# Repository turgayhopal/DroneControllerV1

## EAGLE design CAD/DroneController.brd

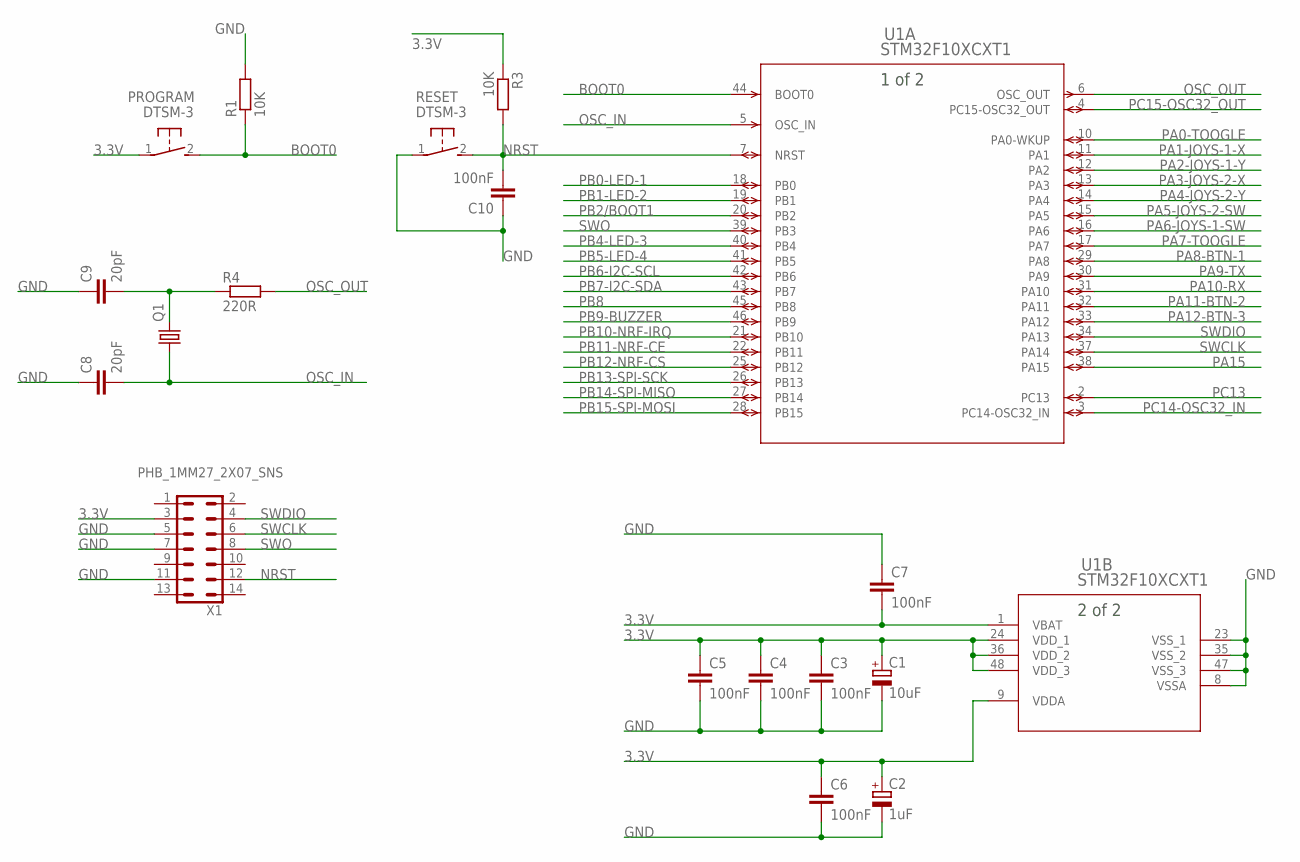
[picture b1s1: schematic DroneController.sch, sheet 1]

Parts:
C1: 10uF; SMC_A
C2: 1uF; SMC_A
C3, C4, C5, C6, C7, C10: 100nF; C0805
C8, C9: 20pF; C0805
PROGRAM: DTSM-3
Q1: CRYSTALHC49S; HC49/S
R1, R3: 10K; R0805
R4: 220R; R0805
RESET: DTSM-3
U1: STM32F10XCXT1; LQFP48-7X7MM
X1: PHB_1MM27_2X07_SNS

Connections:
3.3V: C1.+, C2.+, C3.1, C4.1, C5.1, C6.1, C7.2, PROGRAM.1, R3.1, U1.1 (VBAT), U1.9 (VDDA), U1.24 (VDD_1), U1.36 (VDD_2), U1.48 (VDD_3), X1.3; also elsewhere on the board
BOOT0: PROGRAM.2, R1.1, U1.44 (BOOT0)
GND: C1.-, C2.-, C3.2, C4.2, C5.2, C6.2, C7.1, C8.1, C9.1, C10.1, R1.2, RESET.1, U1.8 (VSSA), U1.23 (VSS_1), U1.35 (VSS_2), U1.47 (VSS_3), X1.5, X1.7, X1.11; also elsewhere on the board
unnamed: C9.2, Q1.2, R4.1
NRST: C10.2, R3.2, RESET.2, U1.7 (NRST), X1.12
OSC_IN: C8.2, Q1.1, U1.5 (OSC_IN)
OSC_OUT: R4.2, U1.6 (OSC_OUT)
PA0-TOOGLE: U1.10 (PA0-WKUP); also elsewhere on the board
PA1-JOYS-1-X: U1.11 (PA1); also elsewhere on the board
PA2-JOYS-1-Y: U1.12 (PA2); also elsewhere on the board
PA3-JOYS-2-X: U1.13 (PA3); also elsewhere on the board
PA4-JOYS-2-Y: U1.14 (PA4); also elsewhere on the board
PA5-JOYS-2-SW: U1.15 (PA5); also elsewhere on the board
PA6-JOYS-1-SW: U1.16 (PA6); also elsewhere on the board
PA7-TOOGLE: U1.17 (PA7)
PA8-BTN-1: U1.29 (PA8); also elsewhere on the board
PA9-TX: U1.30 (PA9)
PA10-RX: U1.31 (PA10)
PA11-BTN-2: U1.32 (PA11); also elsewhere on the board
PA12-BTN-3: U1.33 (PA12); also elsewhere on the board
PA15: U1.38 (PA15)
PB0-LED-1: U1.18 (PB0); also elsewhere on the board
PB1-LED-2: U1.19 (PB1); also elsewhere on the board
PB2/BOOT1: U1.20 (PB2)
PB4-LED-3: U1.40 (PB4); also elsewhere on the board
PB5-LED-4: U1.41 (PB5); also elsewhere on the board
PB6-I2C-SCL: U1.42 (PB6); also elsewhere on the board
PB7-I2C-SDA: U1.43 (PB7); also elsewhere on the board
PB8: U1.45 (PB8)
PB9-BUZZER: U1.46 (PB9)
PB10-NRF-IRQ: U1.21 (PB10); also elsewhere on the board
PB11-NRF-CE: U1.22 (PB11); also elsewhere on the board
PB12-NRF-CS: U1.25 (PB12); also elsewhere on the board
PB13-SPI-SCK: U1.26 (PB13); also elsewhere on the board
PB14-SPI-MISO: U1.27 (PB14); also elsewhere on the board
PB15-SPI-MOSI: U1.28 (PB15); also elsewhere on the board
PC13: U1.2 (PC13)
PC14-OSC32_IN: U1.3 (PC14-OSC32_IN)
PC15-OSC32_OUT: U1.4 (PC15-OSC32_OUT)
SWCLK: U1.37 (PA14), X1.6
SWDIO: U1.34 (PA13), X1.4
SWO: U1.39 (PB3), X1.8

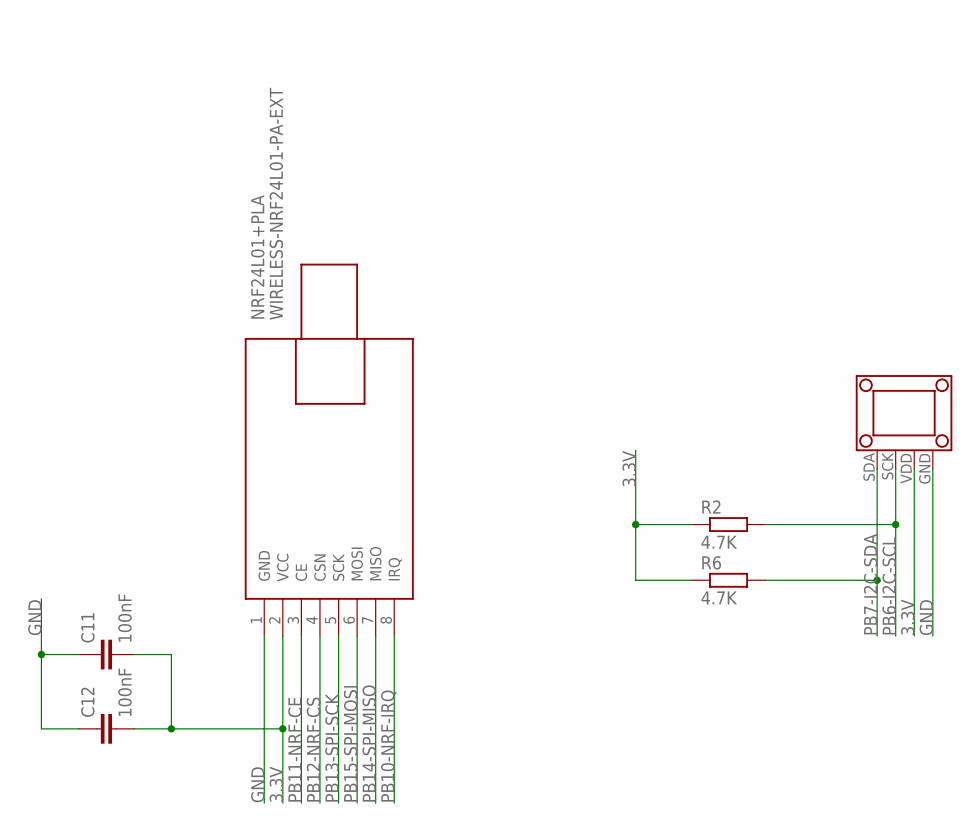
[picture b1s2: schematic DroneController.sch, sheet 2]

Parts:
C11, C12: 100nF; C0805
NRF24L01+PLA: WIRELESS-NRF24L01-PA-EXT
R2, R6: 4.7K; R0805
U$1: 1.3_TFT_OLED

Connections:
3.3V: C11.2, C12.2, NRF24L01+PLA.2 (VCC), R2.1, R6.1, U$1.VDD; also elsewhere on the board
GND: C11.1, C12.1, NRF24L01+PLA.1 (GND), U$1.GND; also elsewhere on the board
PB6-I2C-SCL: R2.2, U$1.SCK; also elsewhere on the board
PB7-I2C-SDA: R6.2, U$1.SDA; also elsewhere on the board
PB10-NRF-IRQ: NRF24L01+PLA.8 (IRQ); also elsewhere on the board
PB11-NRF-CE: NRF24L01+PLA.3 (CE); also elsewhere on the board
PB12-NRF-CS: NRF24L01+PLA.4 (CSN); also elsewhere on the board
PB13-SPI-SCK: NRF24L01+PLA.5 (SCK); also elsewhere on the board
PB14-SPI-MISO: NRF24L01+PLA.7 (MISO); also elsewhere on the board
PB15-SPI-MOSI: NRF24L01+PLA.6 (MOSI); also elsewhere on the board

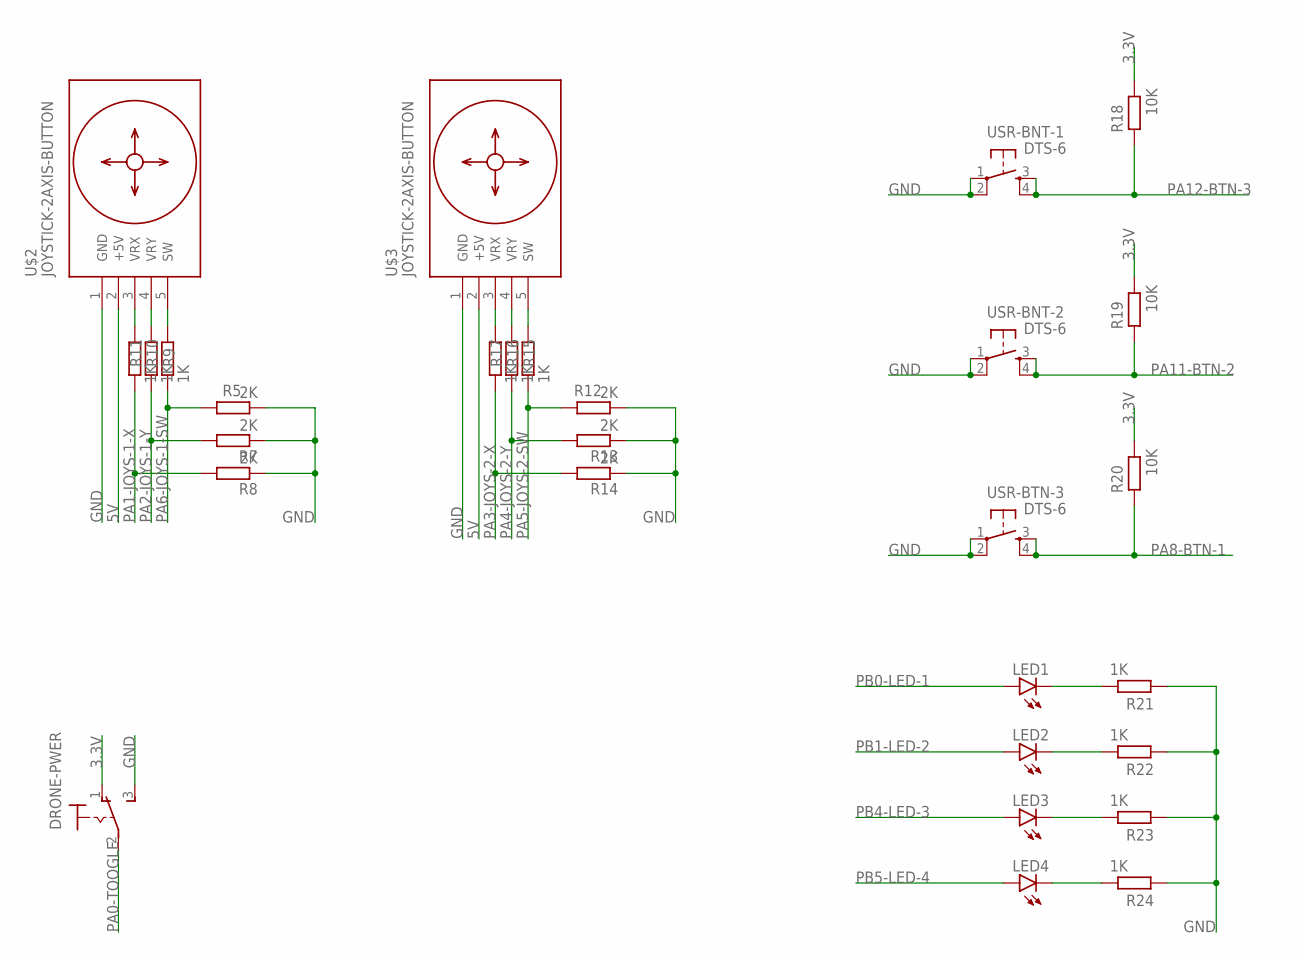
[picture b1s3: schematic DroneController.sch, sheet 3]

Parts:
DRONE-PWER: M9040P
LED1, LED2, LED3, LED4: LEDCHIP-LED0805; CHIP-LED0805
R5, R7, R8, R12, R13, R14: 2K; R0805
R9, R10, R11, R15, R16, R17, R21, R22, R23, R24: 1K; R0805
R18, R19, R20: 10K; R0805
U$2, U$3: JOYSTICK-2AXIS-BUTTON
USR-BNT-1, USR-BNT-2: DTS-6
USR-BTN-3: DTS-6

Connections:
3.3V: DRONE-PWER.1 (O), R18.1, R19.1, R20.1; also elsewhere on the board
5V: U$2.2 (+5V), U$3.2 (+5V); also elsewhere on the board
GND: DRONE-PWER.3 (S), R5.1, R7.1, R8.1, R12.1, R13.1, R14.1, R21.2, R22.2, R23.2, R24.2, U$2.1 (GND), U$3.1 (GND), USR-BNT-1.1, USR-BNT-1.2, USR-BNT-2.1, USR-BNT-2.2, USR-BTN-3.1, USR-BTN-3.2; also elsewhere on the board
unnamed: R11.2, U$2.3 (VRX)
unnamed: R10.2, U$2.4 (VRY)
unnamed: R9.2, U$2.5 (SW)
unnamed: R17.2, U$3.3 (VRX)
unnamed: R16.2, U$3.4 (VRY)
unnamed: LED4.C, R24.1
unnamed: R15.2, U$3.5 (SW)
unnamed: LED3.C, R23.1
unnamed: LED2.C, R22.1
unnamed: LED1.C, R21.1
PA0-TOOGLE: DRONE-PWER.2; also elsewhere on the board
PA1-JOYS-1-X: R8.2, R11.1; also elsewhere on the board
PA2-JOYS-1-Y: R7.2, R10.1; also elsewhere on the board
PA3-JOYS-2-X: R14.2, R17.1; also elsewhere on the board
PA4-JOYS-2-Y: R13.2, R16.1; also elsewhere on the board
PA5-JOYS-2-SW: R12.2, R15.1; also elsewhere on the board
PA6-JOYS-1-SW: R5.2, R9.1; also elsewhere on the board
PA8-BTN-1: R20.2, USR-BTN-3.3, USR-BTN-3.4; also elsewhere on the board
PA11-BTN-2: R19.2, USR-BNT-2.3, USR-BNT-2.4; also elsewhere on the board
PA12-BTN-3: R18.2, USR-BNT-1.3, USR-BNT-1.4; also elsewhere on the board
PB0-LED-1: LED1.A; also elsewhere on the board
PB1-LED-2: LED2.A; also elsewhere on the board
PB4-LED-3: LED3.A; also elsewhere on the board
PB5-LED-4: LED4.A; also elsewhere on the board

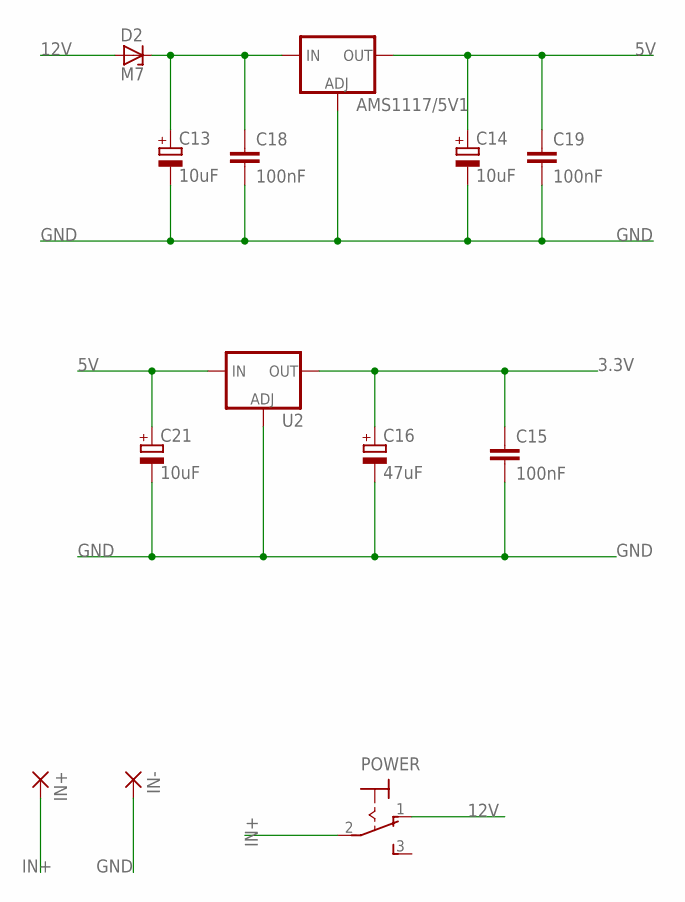
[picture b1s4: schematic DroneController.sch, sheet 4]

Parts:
AMS1117/5V1: V_REG_LM1117SOT223; SOT223
C13, C14, C21: 10uF; SMC_A
C15, C18, C19: 100nF; C0805
C16: 47uF; SMC_B
D2: M7; DO214AC
IN+: 2,15/1,0
IN-: 2,15/1,0
POWER: M9040P
U2: V_REG_LM1117SOT223; SOT223

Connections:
3.3V: C15.1, C16.+, U2.2 (OUT), U2.4 (OUT); also elsewhere on the board
5V: AMS1117/5V1.2 (OUT), AMS1117/5V1.4 (OUT), C14.+, C19.1, C21.+, U2.3 (IN); also elsewhere on the board
12V: D2.A, POWER.1 (O)
GND: AMS1117/5V1.1 (ADJ), C13.-, C14.-, C15.2, C16.-, C18.2, C19.2, C21.-, IN-.1, U2.1 (ADJ); also elsewhere on the board
IN+: IN+.1, POWER.2
unnamed: AMS1117/5V1.3 (IN), C13.+, C18.1, D2.C

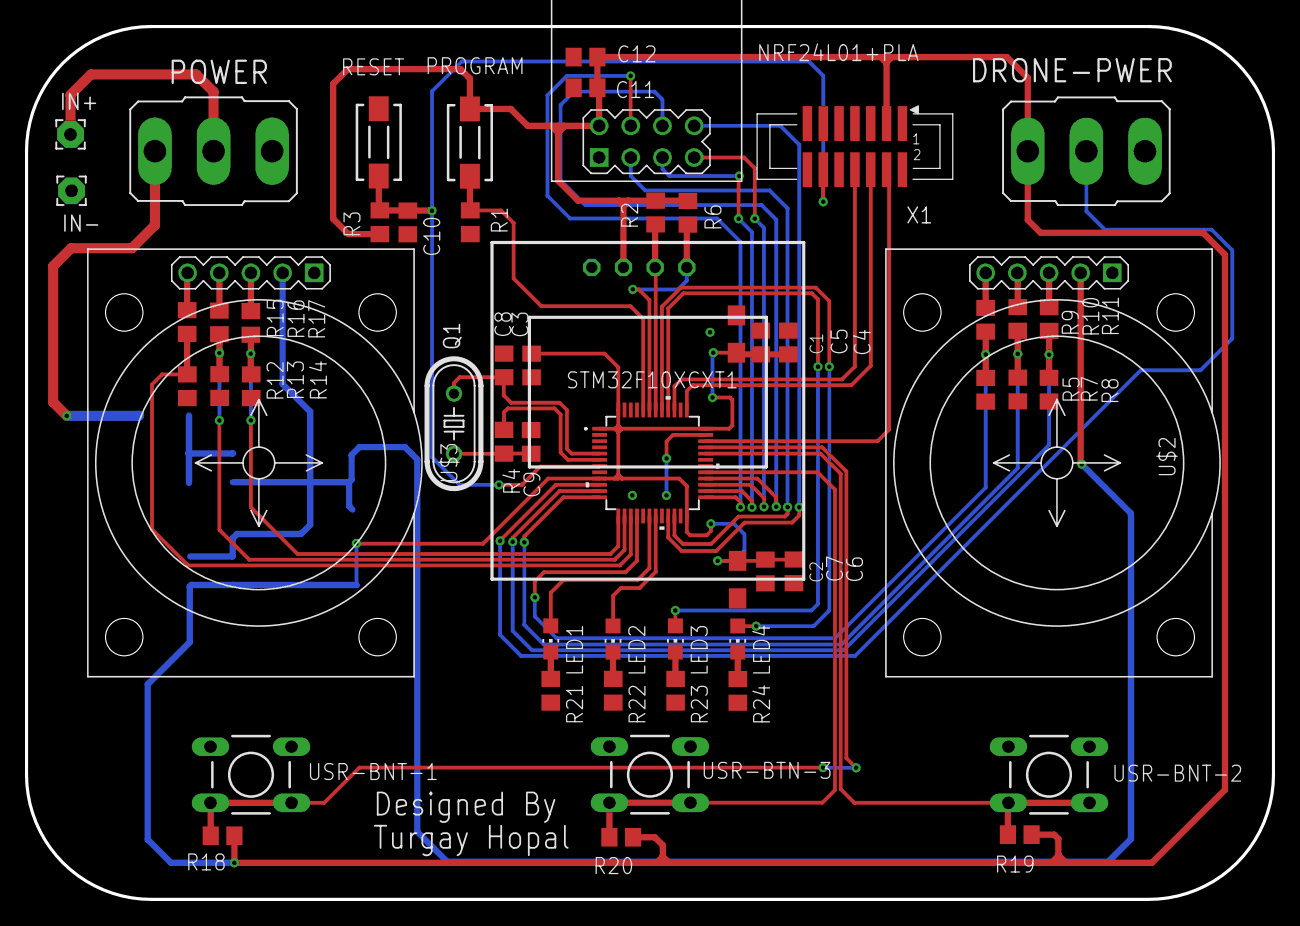
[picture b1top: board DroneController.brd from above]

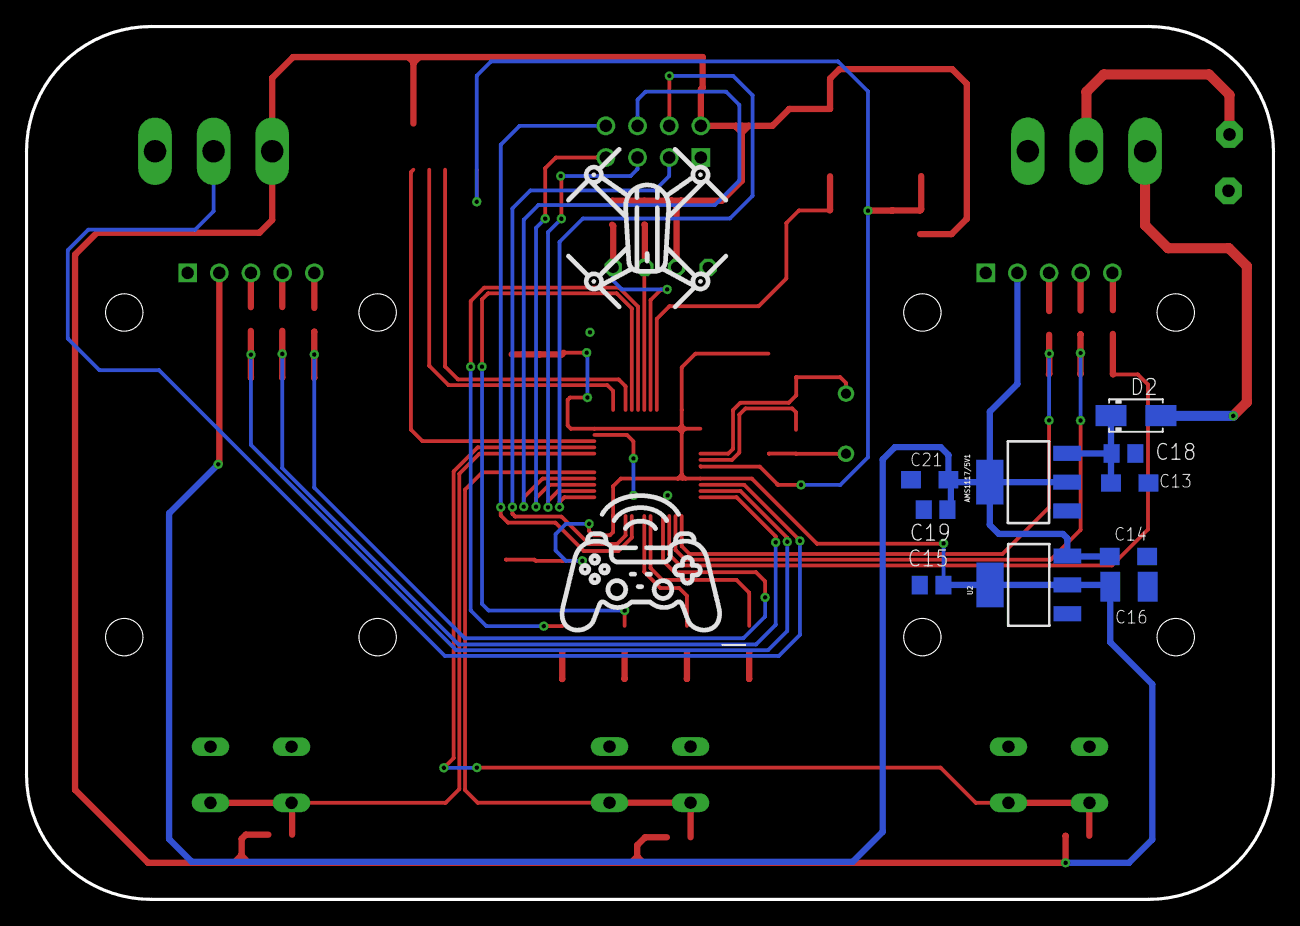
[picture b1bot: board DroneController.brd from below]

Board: 2 copper layers, 100.0 x 70.0 mm, 66 parts (10 on the bottom side), 46 nets.

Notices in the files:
parts and their libraries:
SparkFun-IC-Power: Licensing: Creative Commons ShareAlike 4.0 International - https://creativecommons.org/licenses/by-sa/4.0
diy-modules: Released under the Creative Commons Attribution 4.0 International License: http://creativecommons.org/licenses/by/4.0
